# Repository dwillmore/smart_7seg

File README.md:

# smart_7seg
Smart 7 segment display driver board

This board carries two 2 digit 7 segment displays and multiplexes them to display up to four characters.
Input is serial ASCII at 115200 baud.  The board will display the first four characters it sees after a newline or carrage return.  It will then pass through any remaining characters until the next carrage return or newline.  This allows boards to be cascaded from left to right to add more digits to the display in a manner that is invisible to the user.

The board is based off of the WCH CH32V003 chip in a TSSOP20 pin package.  It has an 0604 1uF capacitor as a decoupling cap and four AO3416 mosfets for the digit drivers.  It is designed to run at 3.3V and works with standard red and green displays.  It may also work with modern GaN displays, but that has not been tested.

The boards were fabricated by JLCPCB and designed with KiCAD 8.0.
Schematic:

Front Copper:

Back Copper:

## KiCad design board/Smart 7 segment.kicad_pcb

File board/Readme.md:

# KiCAD and fabrication files for JLCPCB

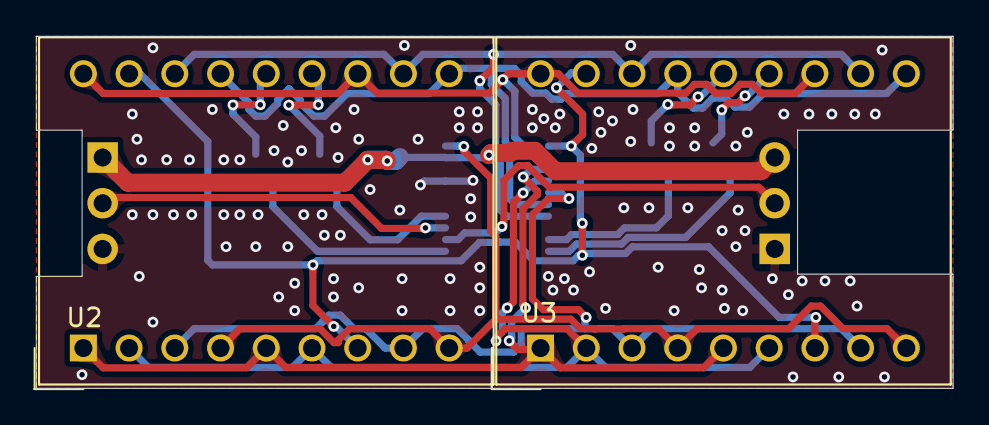
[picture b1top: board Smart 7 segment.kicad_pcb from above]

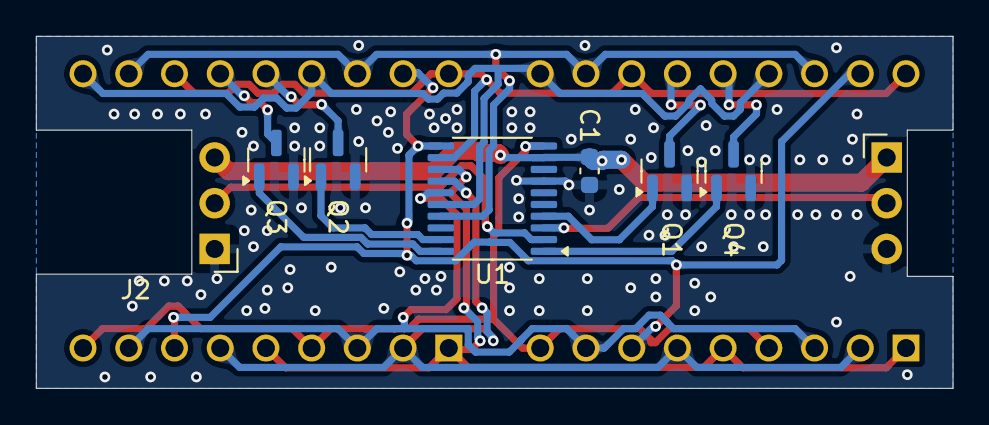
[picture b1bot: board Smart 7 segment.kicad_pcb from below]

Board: 2 copper layers, 50.9 x 19.6 mm, 10 parts (8 on the bottom side), 20 nets.

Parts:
C1: C; C_0603_1608Metric
J1, J2: Conn_01x03_Pin; PinHeader_1x03_P2.54mm_Horizontal
Q1, Q2, Q3, Q4: AO3400A; SOT-23
U1: CH32V003FxPx; TSSOP-20_4.4x6.5mm_P0.65mm
U2, U3: DC56-11CGKWA; DA56-11CGKWA

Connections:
GND: C1.2, J1.3, J2.1, Q1.2 (S), Q2.2 (S), Q3.2 (S), Q4.2 (S), U1.7 (VSS)
unnamed: J1.2, U1.3 (PD6)
unnamed: J2.2, U1.2 (PD5)
unnamed: Q1.3 (D), U2.13 (DIG2_CC)
unnamed: Q1.1 (G), U1.4 (PD7)
unnamed: Q2.3 (D), U3.14 (DIG1_CC)
unnamed: Q2.1 (G), U1.19 (PD2)
unnamed: Q3.3 (D), U3.13 (DIG2_CC)
unnamed: Q3.1 (G), U1.20 (PD3)
unnamed: Q4.3 (D), U2.14 (DIG1_CC)
unnamed: Q4.1 (G), U1.1 (PD4)
unnamed: U1.10 (PC0), U2.4 (DP1), U2.9 (DP2), U3.4 (DP1), U3.9 (DP2)
unnamed: U1.11 (PC1), U2.7 (DIG2_G), U2.17 (DIG1_G), U3.7 (DIG2_G), U3.17 (DIG1_G)
unnamed: U1.12 (PC2), U2.12 (DIG2_F), U2.18 (DIG1_F), U3.12 (DIG2_F), U3.18 (DIG1_F)
unnamed: U1.13 (PC3), U2.1 (DIG1_E), U2.5 (DIG2_E), U3.1 (DIG1_E), U3.5 (DIG2_E)
unnamed: U1.14 (PC4), U2.2 (DIG1_D), U2.6 (DIG2_D), U3.2 (DIG1_D), U3.6 (DIG2_D)
unnamed: U1.15 (PC5), U2.3 (DIG1_C), U2.8 (DIG2_C), U3.3 (DIG1_C), U3.8 (DIG2_C)
unnamed: U1.16 (PC6), U2.10 (DIG2_B), U2.15 (DIG1_B), U3.10 (DIG2_B), U3.15 (DIG1_B)
unnamed: U1.17 (PC7), U2.11 (DIG2_A), U2.16 (DIG1_A), U3.11 (DIG2_A), U3.16 (DIG1_A)
VCC: C1.1, J1.1, J2.3, U1.9 (VDD)

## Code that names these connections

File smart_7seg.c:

#include "ch32v003fun.h"
#include <stdio.h>

#include "font.h"

#define digit0 PD4
#define digit1 PD7
#define digit2 PD2
#define digit3 PD3
#define num_digits 4

uint8_t digits[] = {	digit0,
											digit1,
											digit2,
											digit3 };

#define segmentA PC7
#define segmentB PC6
#define segmentC PC5
#define segmentD PC4
#define segmentE PC3
#define segmentF PC2
#define segmentG PC1
#define segmentDP PC0
#define num_segments 8

uint8_t segments[] = {  segmentA,
												segmentB,
												segmentC,
												segmentD,
												segmentE,
												segmentF,
												segmentG,
												segmentDP };

uint power[] = {1000, 100, 10, 1};
volatile uint current_digit = 0;
volatile uint8_t display_buf[num_digits];

#define SYSTICK_DELAY ((uint32_t)FUNCONF_SYSTEM_CORE_CLOCK / 1000)

void setDigit(uint8_t character){
	for(int i=0; i < num_segments; i++)
		if(font[character] & 1<<i)
			funDigitalWrite( segments[i], FUN_HIGH )
		else
			funDigitalWrite( segments[i], FUN_LOW );
}

void SysTick_Handler(void) __attribute__((interrupt));
void SysTick_Handler(void)
{
	SysTick->CMP += SYSTICK_DELAY;
	SysTick->SR = 0x00000000;
	for(int i = 0; i < num_digits; i++)
		funDigitalWrite( digits[i], FUN_LOW);
	setDigit(display_buf[current_digit]);
	funDigitalWrite( digits[current_digit], FUN_HIGH);
	if(current_digit++ == num_digits)
		current_digit = 0;
}

int main()
{
	uint count = 0;
	uint loops = 0;
	SystemInit();
	funGpioInitAll();
	enum State_t {  First_char,
									Second_char,
									Third_char,
									Fourth_char,
									Passthrough,
									EOL_ignore };
	enum State_t State = First_char;
	uint8_t in_char;
	
	// Setup digit select pins
	for(int i=0; i < num_digits; i++){
		funPinMode( digits[i], GPIO_Speed_2MHz | GPIO_CNF_OUT_PP );
		funDigitalWrite( digits[i], FUN_LOW );
	}

  // Setup segment pins
	for(int i=0; i < num_segments; i++){
		funPinMode( segments[i], GPIO_Speed_2MHz | GPIO_CNF_OUT_PP );
	  funDigitalWrite( segments[i], FUN_LOW );
	}

  // Setup serial pins and function
	SetupUART( UART_BRR );
	funPinMode( PD6, GPIO_CNF_IN_FLOATING );
	USART1->CTLR1 |= USART_CTLR1_RE;

  // Setup SysTicK based IRQ routine to run once a ms
	SysTick->CTLR = 0x0000;
	SysTick->CMP = SYSTICK_DELAY - 1;
	SysTick->CNT = 0x00000000;
	SysTick->CTLR |= SYSTICK_CTLR_STE | SYSTICK_CTLR_STIE | SYSTICK_CTLR_STCLK;
	NVIC_EnableIRQ(SysTicK_IRQn);

	for(int i = 0; i < num_digits; i++)
		display_buf[i] = 0;

	while(1)
	{
	  if(USART1->STATR & USART_STATR_RXNE){
			in_char = USART1->DATAR;
			switch(State){
				case First_char:
					display_buf[0] = in_char;
					State = Second_char;
					break;
				case Second_char:
					display_buf[1] = in_char;
					State = Third_char;
					break;
				case Third_char:
					display_buf[2] = in_char;
					State = Fourth_char;
					break;
				case Fourth_char:
					display_buf[3] = in_char;
					State = Passthrough;
					break;
				case Passthrough:
					if((in_char == 13) || (in_char == 10))
						State = EOL_ignore;
					printf("%c", in_char);
					break;
				case EOL_ignore:
					if((in_char == 13) || (in_char == 10)){
					  printf("%c", in_char);
					}else{
					  display_buf[0] = in_char;
						State = Second_char;
					}
					break;
			}
		}
	}
	while(1)
	{
		for(int dig=0; dig<num_digits; dig++){
			display_buf[dig] = ((count/power[dig])%10 + 48);
		}
		Delay_Ms(1);
		if(loops++ > 9){
			loops = 0;
			if(count++ > 9999) count = 0;
		}
	}
}

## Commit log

2024-11-10 Initial code
2024-11-10 Update README.md
    Add schematic image
2024-11-10 Update README.md
    Add board images
2024-11-10 Add files via upload
    KiCAD source and JLCPCB fab files
2024-11-11 Update README.md
    Replace PCB images.
